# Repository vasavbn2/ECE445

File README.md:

# ECE445
This is our repo for our ECE445 Key FOB project!

## Week of 9/23/24
Discussed our proposal in meeting with our TA.
Next steps: Perform tolerance analysis and begin work on design document.

## Week of 9/30/24
Discussed the design document and design review process with our TA. Working on the proposal regrade, including tolerance analysis and ethics.
Next steps: Complete schematics in KiCad so we have complete schematics and BOMs for our 2 boards. Finish composing the design document.

## Week of 10/7/24
Finalized schematics and started layouts

## Week of 10/14/24
Completed fob layout
BOM for fob: https://www.digikey.com/short/3907nrjb

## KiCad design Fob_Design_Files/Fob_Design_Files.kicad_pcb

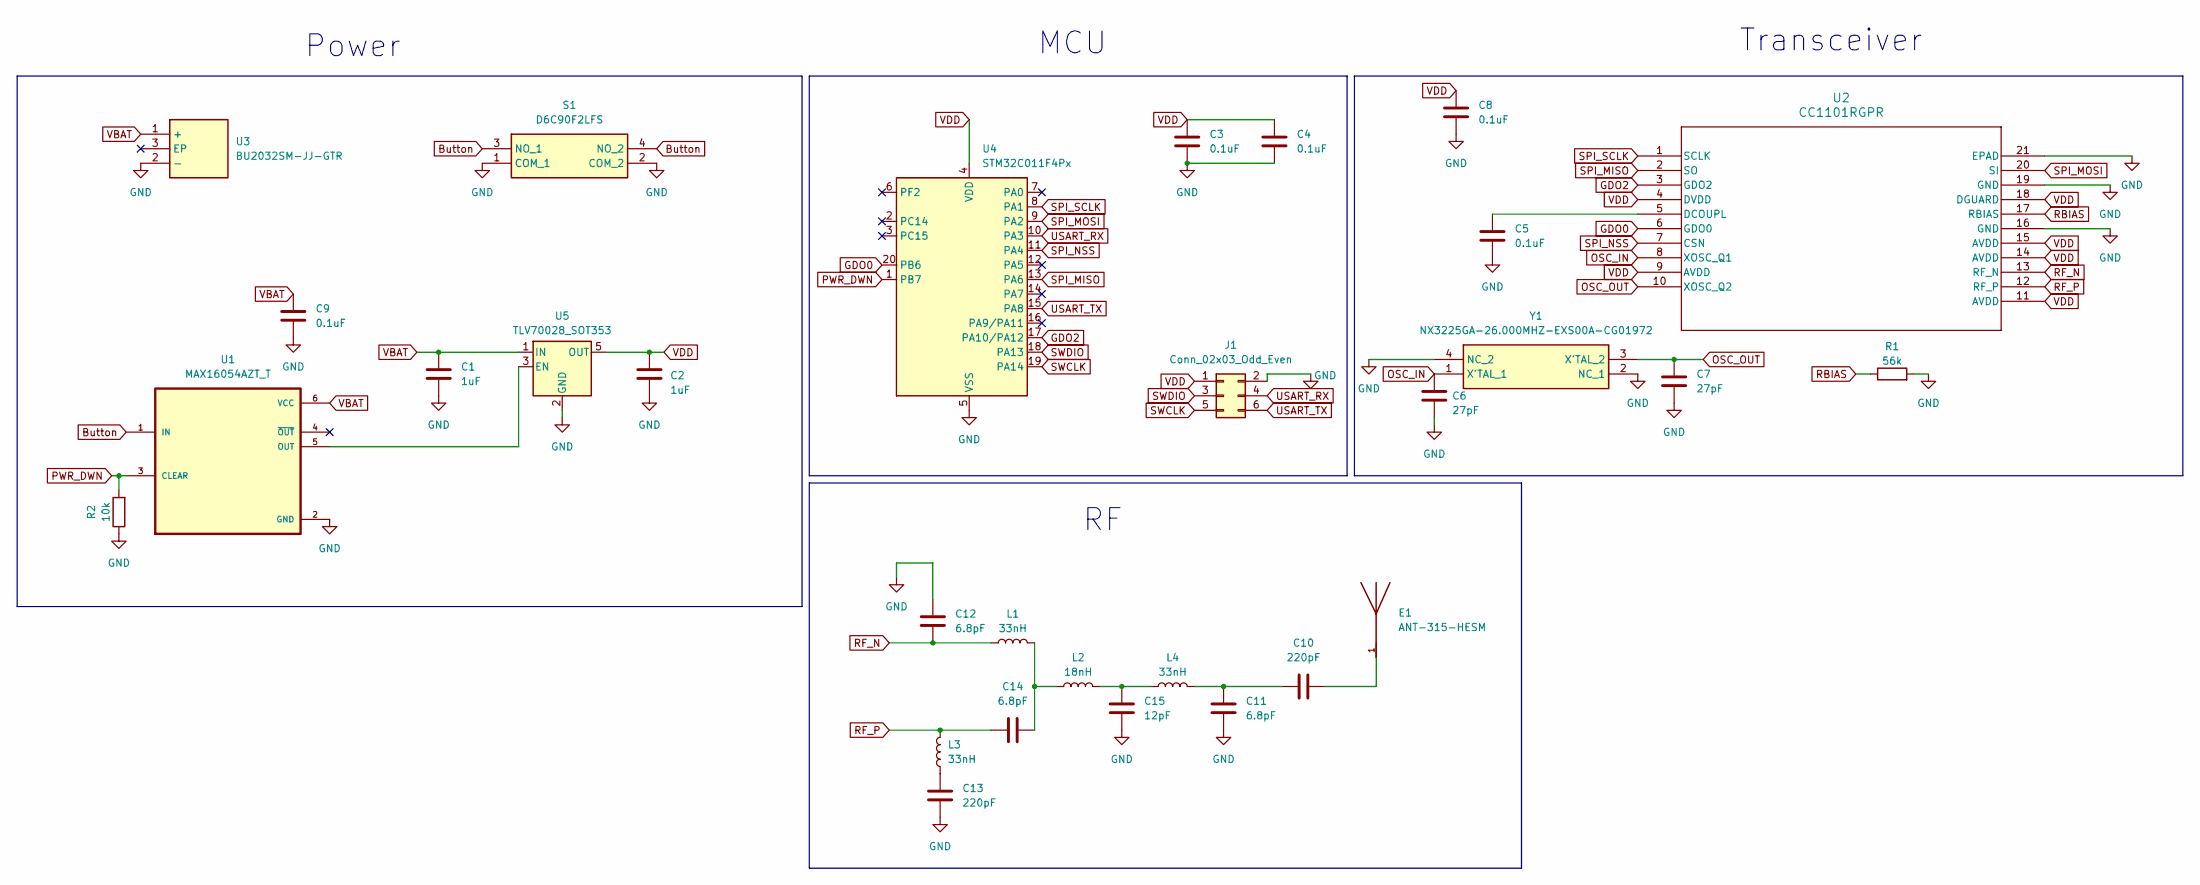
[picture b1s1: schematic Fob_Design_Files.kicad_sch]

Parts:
C1, C2: 1uF; C_0603_1608Metric
C3, C4, C5, C8, C9: 0.1uF; C_0603_1608Metric
C6, C7: 27pF; C_0603_1608Metric
C10, C13: 220pF; C_0603_1608Metric
C11, C12, C14: 6.8pF; C_0603_1608Metric
C15: 12pF; C_0603_1608Metric
E1: ANT-315-HESM; XDCR_ANT-315-HESM; PARTREV B
J1: Conn_02x03_Odd_Even; PinSocket_2x03_P2.54mm_Vertical
L1, L3, L4: 33nH; L_0603_1608Metric
L2: 18nH; L_0603_1608Metric
R1: 56k; L_0603_1608Metric
R2: 10k; L_0603_1608Metric
S1: D6C90F2LFS; Manufacturer_Part_Number D6C90F2LFS; Mouser Part Number 611-D6C90F2LFS
U1: MAX16054AZT_T; SOT95P275X110-6N
U2: CC1101RGPR; RGP20_2P4X2P4
U3: BU2032SM-JJ-GTR; BU2032SMJJGTR; Manufacturer_Part_Number BU2032SM-JJ-GTR
U4: STM32C011F4Px; TSSOP-20_4.4x6.5mm_P0.65mm
U5: TLV70028_SOT353; SOT-353_SC-70-5
Y1: NX3225GA-26.000MHZ-EXS00A-CG01972; NX3225GA16000MSTDCRG1; Mouser Part Number 344-NX3225GA26MHZEXS

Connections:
Button: S1.3 (NO_1), S1.4 (NO_2), U1.1 (IN)
GDO0: U2.6 (GDO0), U4.20 (PB6)
GDO2: U2.3 (GDO2), U4.17 (PA10/PA12)
GND: C1.2, C2.2, C3.2, C4.2, C5.2, C6.2, C7.2, C8.2, C9.2, C11.1, C12.2, C13.1, C15.1, J1.2, R1.2, R2.1, S1.1 (COM_1), S1.2 (COM_2), U1.2 (GND), U2.16 (GND), U2.19 (GND), U2.21 (EPAD), U3.2 (-), U4.5 (VSS), U5.2 (GND), Y1.2 (NC_1), Y1.4 (NC_2)
unnamed: C10.1, C11.2, L4.2
unnamed: C10.2, E1.1
unnamed: C13.2, L3.1
unnamed: C14.1, L1.2, L2.1
unnamed: C15.2, L2.2, L4.1
unnamed: U1.5 (OUT), U5.3 (EN)
unnamed: C5.1, U2.5 (DCOUPL)
OSC_IN: C6.1, U2.8 (XOSC_Q1), Y1.1 (X'TAL_1)
OSC_OUT: C7.1, U2.10 (XOSC_Q2), Y1.3 (X'TAL_2)
PWR_DWN: R2.2, U1.3 (CLEAR), U4.1 (PB7)
RBIAS: R1.1, U2.17 (RBIAS)
RF_N: C12.1, L1.1, U2.13 (RF_N)
RF_P: C14.2, L3.2, U2.12 (RF_P)
SPI_MISO: U2.2 (SO), U4.13 (PA6)
SPI_MOSI: U2.20 (SI), U4.9 (PA2)
SPI_NSS: U2.7 (CSN), U4.11 (PA4)
SPI_SCLK: U2.1 (SCLK), U4.8 (PA1)
SWCLK: J1.5, U4.19 (PA14)
SWDIO: J1.3, U4.18 (PA13)
USART_RX: J1.4, U4.10 (PA3)
USART_TX: J1.6, U4.15 (PA8)
VBAT: C1.1, C9.1, U1.6 (VCC), U3.1 (+), U5.1 (IN)
VDD: C2.1, C3.1, C4.1, C8.1, J1.1, U2.4 (DVDD), U2.9 (AVDD), U2.11 (AVDD), U2.14 (AVDD), U2.15 (AVDD), U2.18 (DGUARD), U4.4 (VDD), U5.5 (OUT)

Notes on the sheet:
Power
MCU
Transceiver

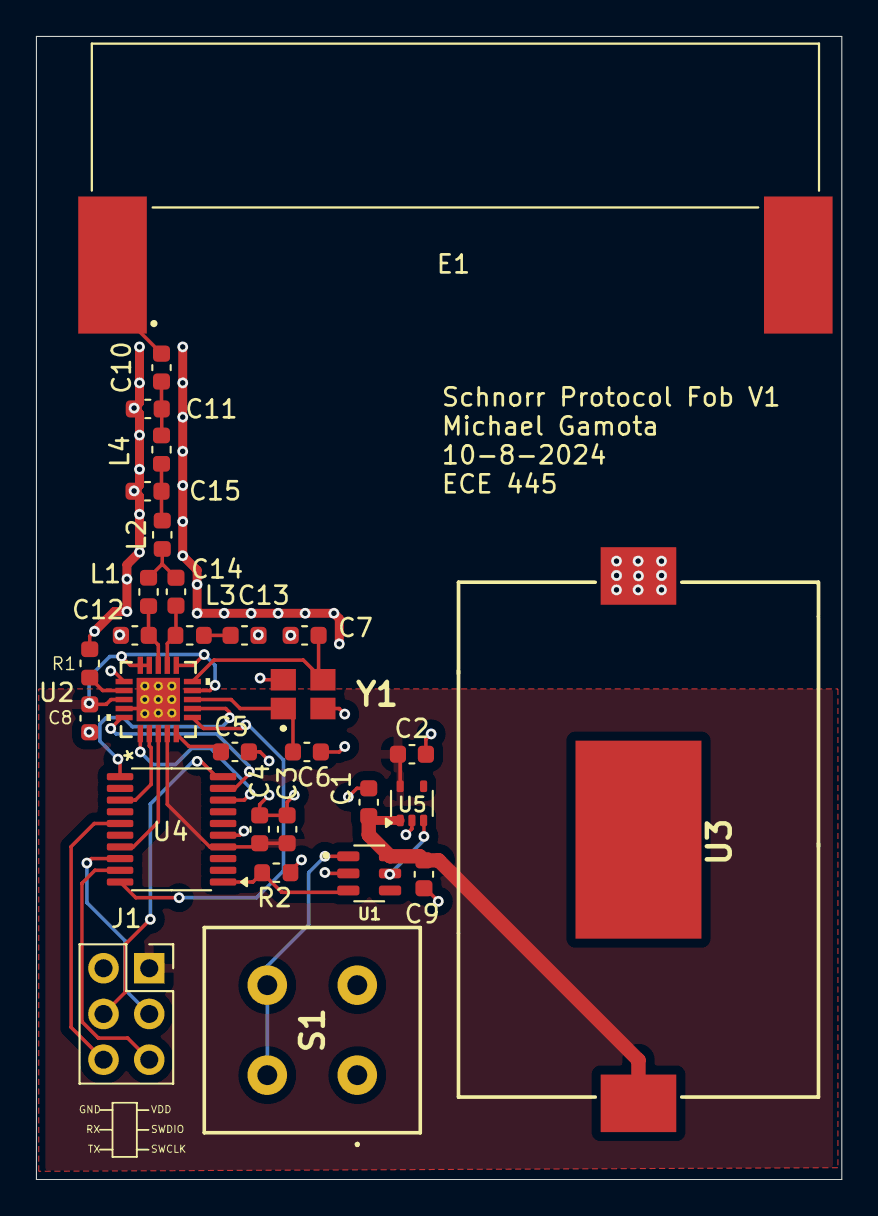
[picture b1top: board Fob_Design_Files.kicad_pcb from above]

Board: 2 copper layers, 44.7 x 63.5 mm, 30 parts (0 on the bottom side), 27 nets.

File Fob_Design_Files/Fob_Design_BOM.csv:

Reference,Value,Datasheet,Footprint,Qty,DNP
"C1,C2",1uF,~,Capacitor_SMD:C_0603_1608Metric,2,
"C3,C4,C5,C8,C9",0.1uF,~,Capacitor_SMD:C_0603_1608Metric,5,
"C6,C7",27pF,~,Capacitor_SMD:C_0603_1608Metric,2,
"C10,C13",220pF,~,Capacitor_SMD:C_0603_1608Metric,2,
"C11,C12,C14",6.8pF,~,Capacitor_SMD:C_0603_1608Metric,3,
C15,12pF,~,Capacitor_SMD:C_0603_1608Metric,1,
E1,ANT-315-HESM,,ANT-315-HESM:XDCR_ANT-315-HESM,1,
J1,Conn_02x03_Odd_Even,~,Connector_PinSocket_2.54mm:PinSocket_2x03_P2.54mm_Vertical,1,
"L1,L3,L4",33nH,~,Inductor_SMD:L_0603_1608Metric,3,
L2,18nH,~,Inductor_SMD:L_0603_1608Metric,1,
R1,56k,~,Inductor_SMD:L_0603_1608Metric,1,
R2,10k,~,Inductor_SMD:L_0603_1608Metric,1,
S1,D6C90F2LFS,https://www.ckswitches.com/media/1341/d6.pdf,SamacSys_Parts:D6C90F2LFS,1,
U1,MAX16054AZT_T,,MAX16054AZT_T:SOT95P275X110-6N,1,
U2,CC1101RGPR,CC1101RGPR,CC1101:RGP20_2P4X2P4,1,
U3,BU2032SM-JJ-GTR,https://datasheet.datasheetarchive.com/originals/dk/DKDS-14/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,SamacSys_Parts:BU2032SMJJGTR,1,
U4,STM32C011F4Px,https://www.st.com/resource/en/datasheet/stm32c011f4.pdf,Package_SO:TSSOP-20_4.4x6.5mm_P0.65mm,1,
U5,TLV70028_SOT353,http://www.ti.com/lit/ds/symlink/tlv700.pdf,Package_TO_SOT_SMD:SOT-353_SC-70-5,1,
Y1,NX3225GA-26.000MHZ-EXS00A-CG01972,https://media.digikey.com/pdf/Data%20Sheets/NDK%20PDFs/NX3225GA.pdf,SamacSys_Parts:NX3225GA16000MSTDCRG1,1,

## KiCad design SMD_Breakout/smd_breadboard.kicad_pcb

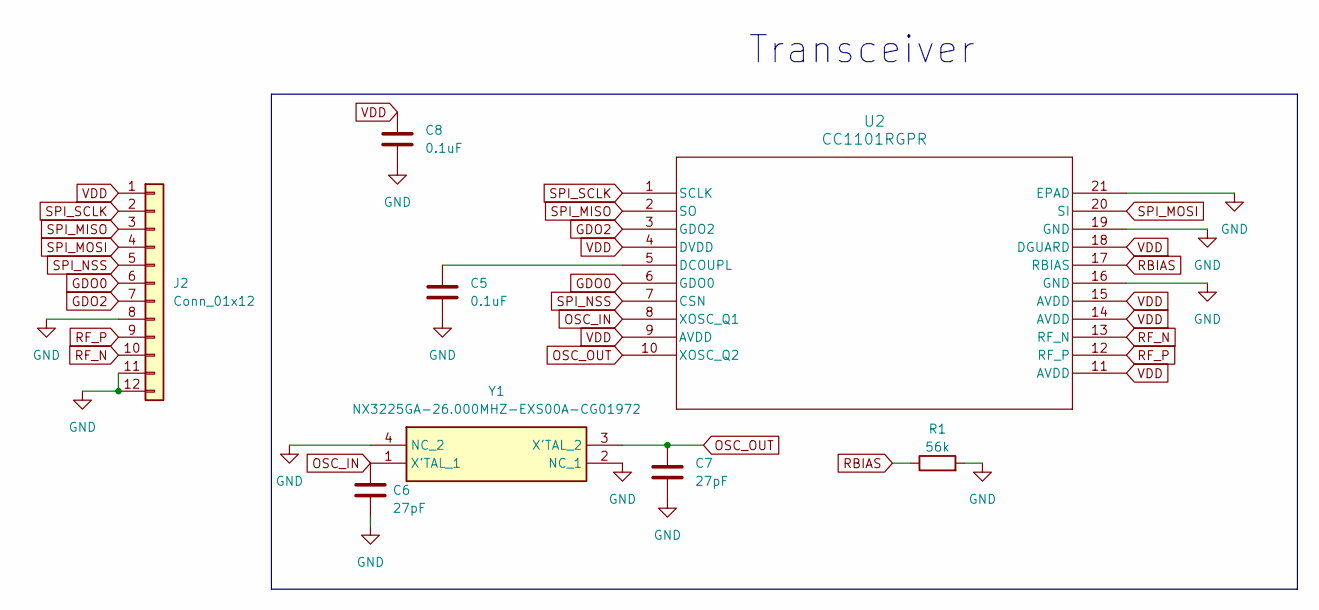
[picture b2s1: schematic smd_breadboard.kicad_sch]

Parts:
C5, C8: 0.1uF; C_0603_1608Metric
C6, C7: 27pF; C_0603_1608Metric
J2: Conn_01x12; PinSocket_1x12_P2.54mm_Horizontal
R1: 56k; L_0603_1608Metric
U2: CC1101RGPR; Texas_RGP0020H_VQFN-20-1EP_4x4mm_P0.5mm_EP2.4x2.4mm
Y1: NX3225GA-26.000MHZ-EXS00A-CG01972; NX3225GA16000MSTDCRG1; Mouser Part Number 344-NX3225GA26MHZEXS

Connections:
GDO0: J2.6, U2.6 (GDO0)
GDO2: J2.7, U2.3 (GDO2)
GND: C5.2, C6.2, C7.2, C8.2, J2.8, J2.11, J2.12, R1.2, U2.16 (GND), U2.19 (GND), U2.21 (EPAD), Y1.2 (NC_1), Y1.4 (NC_2)
unnamed: C5.1, U2.5 (DCOUPL)
OSC_IN: C6.1, U2.8 (XOSC_Q1), Y1.1 (X'TAL_1)
OSC_OUT: C7.1, U2.10 (XOSC_Q2), Y1.3 (X'TAL_2)
RBIAS: R1.1, U2.17 (RBIAS)
RF_N: J2.10, U2.13 (RF_N)
RF_P: J2.9, U2.12 (RF_P)
SPI_MISO: J2.3, U2.2 (SO)
SPI_MOSI: J2.4, U2.20 (SI)
SPI_NSS: J2.5, U2.7 (CSN)
SPI_SCLK: J2.2, U2.1 (SCLK)
VDD: C8.1, J2.1, U2.4 (DVDD), U2.9 (AVDD), U2.11 (AVDD), U2.14 (AVDD), U2.15 (AVDD), U2.18 (DGUARD)

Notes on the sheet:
Transceiver

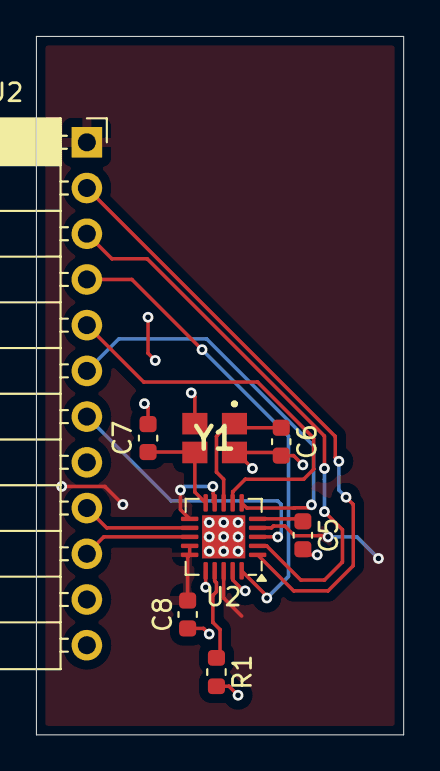
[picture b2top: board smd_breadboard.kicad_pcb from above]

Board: 2 copper layers, 20.4 x 38.8 mm, 8 parts (0 on the bottom side), 14 nets.

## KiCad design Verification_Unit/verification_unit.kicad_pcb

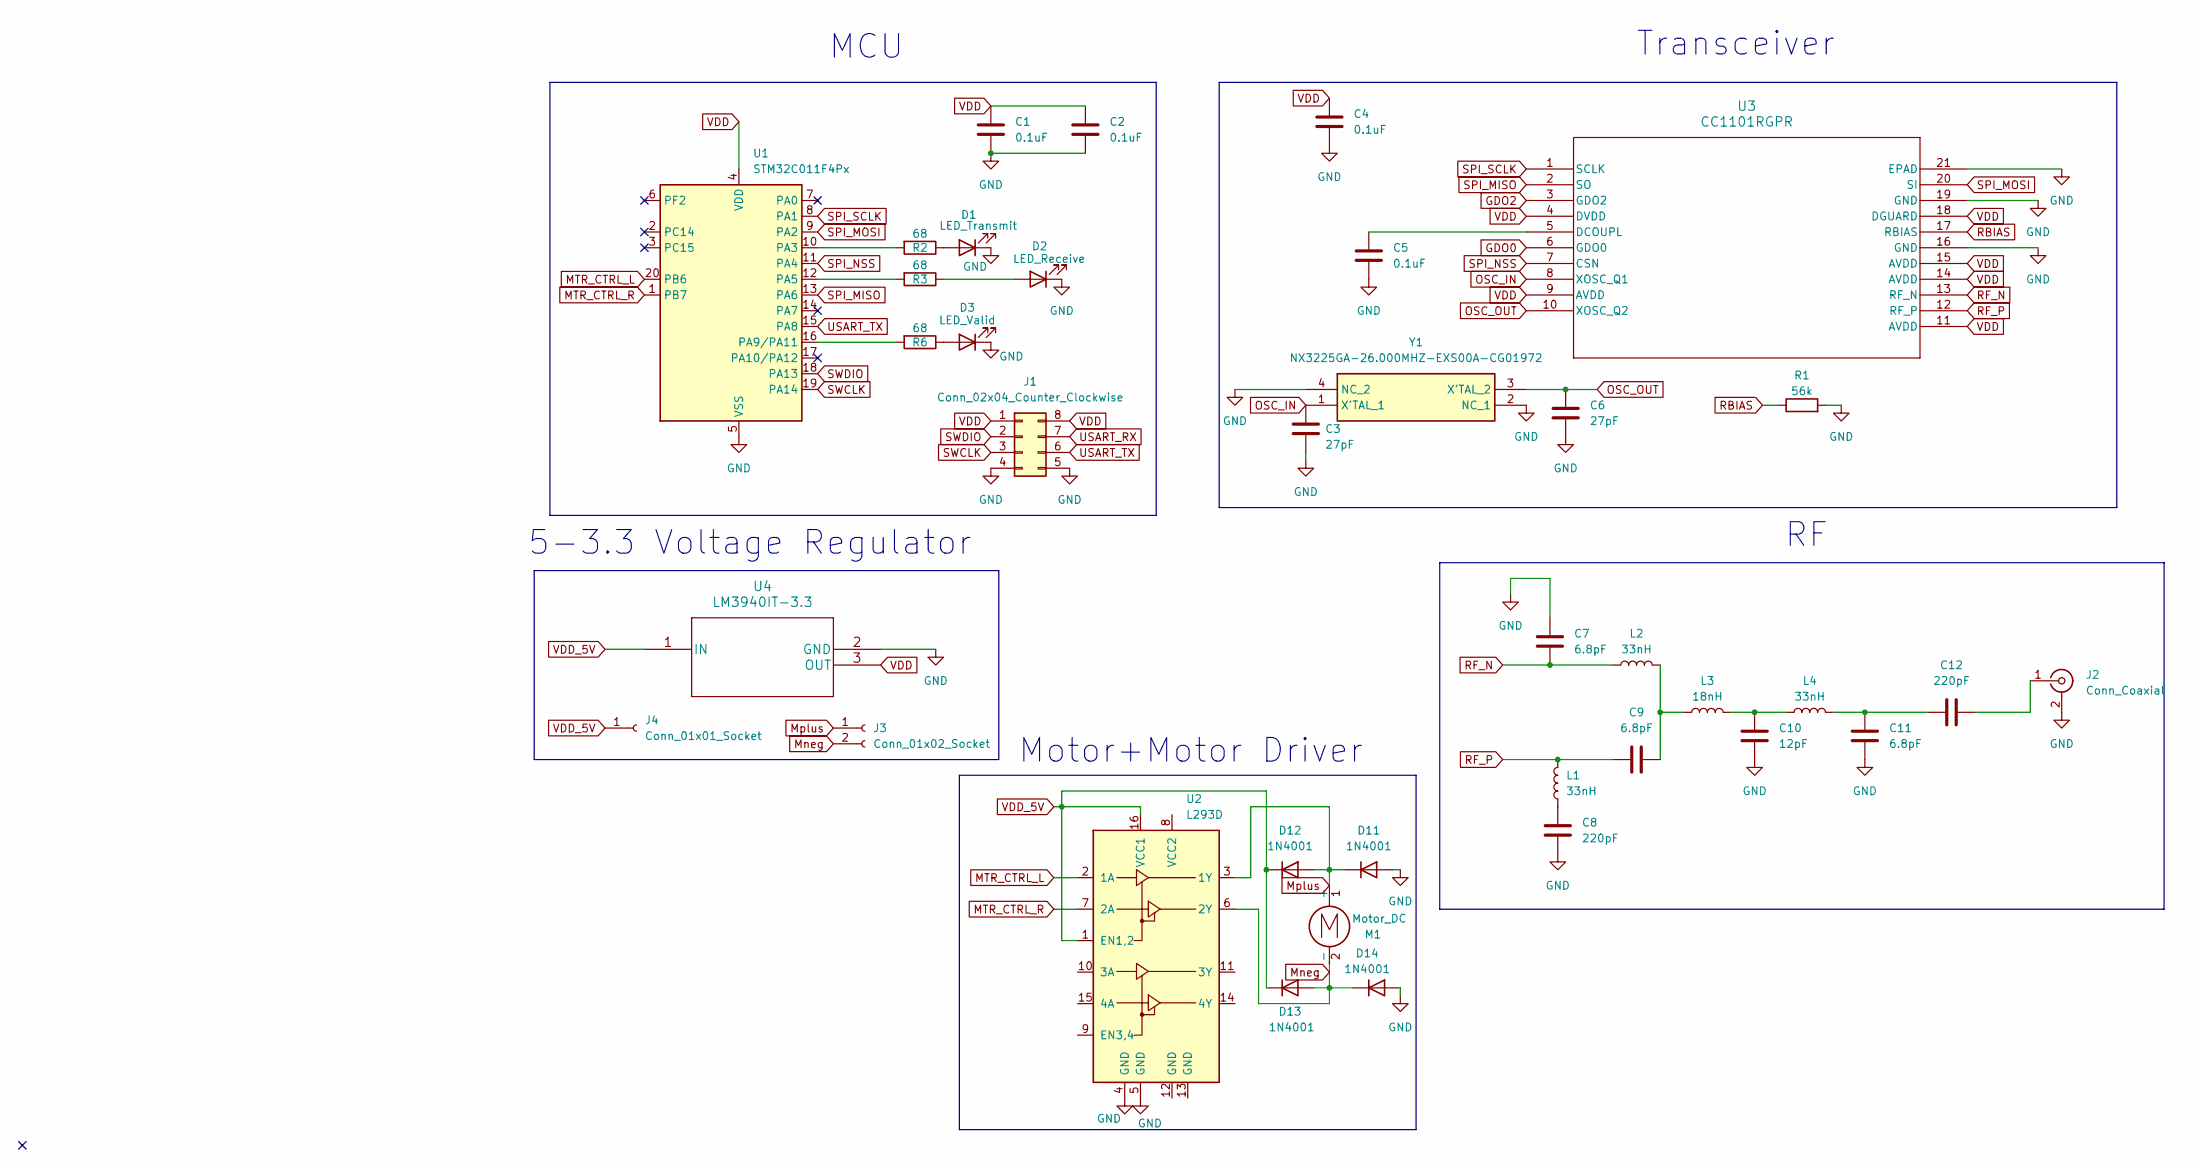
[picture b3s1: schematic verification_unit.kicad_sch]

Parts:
C1, C2, C4, C5: 0.1uF; C_0805_2012Metric
C3, C6: 27pF; C_0805_2012Metric
C7, C9, C11: 6.8pF; C_0805_2012Metric
C8, C12: 220pF; C_0805_2012Metric
C10: 12pF; C_0805_2012Metric
D1: LED_Transmit; LED_0805_2012Metric
D2: LED_Receive; LED_0805_2012Metric
D3: LED_Valid; LED_0805_2012Metric
D11, D12, D13, D14: 1N4001; D_0805_2012Metric
J1: Conn_02x04_Counter_Clockwise; PinSocket_2x04_P2.54mm_Vertical
J2: Conn_Coaxial; SMA_Amphenol_901-143_Horizontal
J3: Conn_01x02_Socket; PinSocket_1x02_P2.54mm_Vertical
J4: Conn_01x01_Socket; PinSocket_1x01_P2.54mm_Vertical
L1, L2, L4: 33nH; L_0805_2012Metric
L3: 18nH; L_0805_2012Metric
M1: Motor_DC
R1: 56k; C_0805_2012Metric
R2, R3, R6: 68; R_0805_2012Metric
U1: STM32C011F4Px; TSSOP-20_4.4x6.5mm_P0.65mm
U2: L293D; DIP-16_W7.62mm
U3: CC1101RGPR; RGP20_2P4X2P4
U4: LM3940IT-3.3
Y1: NX3225GA-26.000MHZ-EXS00A-CG01972; NX3225GA16000MSTDCRG1; Mouser Part Number 344-NX3225GA26MHZEXS

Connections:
GDO0: U3.6 (GDO0)
GDO2: U3.3 (GDO2)
GND: C1.2, C2.2, C3.2, C4.2, C5.2, C6.2, C7.2, C8.1, C10.1, C11.1, D1.1 (K), D2.1 (K), D3.1 (K), D11.2 (A), D14.2 (A), J1.4, J1.5, J2.2 (Ext), R1.2, U1.5 (VSS), U2.4 (GND), U2.5 (GND), U3.16 (GND), U3.19 (GND), U3.21 (EPAD), U4.2 (GND), Y1.2 (NC_1), Y1.4 (NC_2)
MTR_CTRL_L: U1.20 (PB6), U2.2 (1A)
MTR_CTRL_R: U1.1 (PB7), U2.7 (2A)
Mneg: D13.2 (A), D14.1 (K), J3.2, M1.2 (-), U2.6 (2Y)
Mplus: D11.1 (K), D12.2 (A), J3.1, M1.1 (+), U2.3 (1Y)
unnamed: C8.2, L1.1
unnamed: C9.1, L2.2, L3.1
unnamed: C10.2, L3.2, L4.1
unnamed: C11.2, C12.1, L4.2
unnamed: D1.2 (A), R2.1
unnamed: D2.2 (A), R3.1
unnamed: D3.2 (A), R6.1
unnamed: C12.2, J2.1 (In)
unnamed: R2.2, U1.10 (PA3)
unnamed: R3.2, U1.12 (PA5)
unnamed: R6.2, U1.16 (PA9/PA11)
unnamed: C5.1, U3.5 (DCOUPL)
OSC_IN: C3.1, U3.8 (XOSC_Q1), Y1.1 (X'TAL_1)
OSC_OUT: C6.1, U3.10 (XOSC_Q2), Y1.3 (X'TAL_2)
RBIAS: R1.1, U3.17 (RBIAS)
RF_N: C7.1, L2.1, U3.13 (RF_N)
RF_P: C9.2, L1.2, U3.12 (RF_P)
SPI_MISO: U1.13 (PA6), U3.2 (SO)
SPI_MOSI: U1.9 (PA2), U3.20 (SI)
SPI_NSS: U1.11 (PA4), U3.7 (CSN)
SPI_SCLK: U1.8 (PA1), U3.1 (SCLK)
SWCLK: J1.3, U1.19 (PA14)
SWDIO: J1.2, U1.18 (PA13)
USART_RX: J1.7
USART_TX: J1.6, U1.15 (PA8)
VDD: C1.1, C2.1, C4.1, J1.1, J1.8, U1.4 (VDD), U3.4 (DVDD), U3.9 (AVDD), U3.11 (AVDD), U3.14 (AVDD), U3.15 (AVDD), U3.18 (DGUARD), U4.3 (OUT)
VDD_5V: D12.1 (K), D13.1 (K), J4.1, U2.1 (EN1,2), U2.16 (VCC1), U4.1 (IN)

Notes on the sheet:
Transceiver
MCU
Motor+Motor Driver
5-3.3 Voltage Regulator

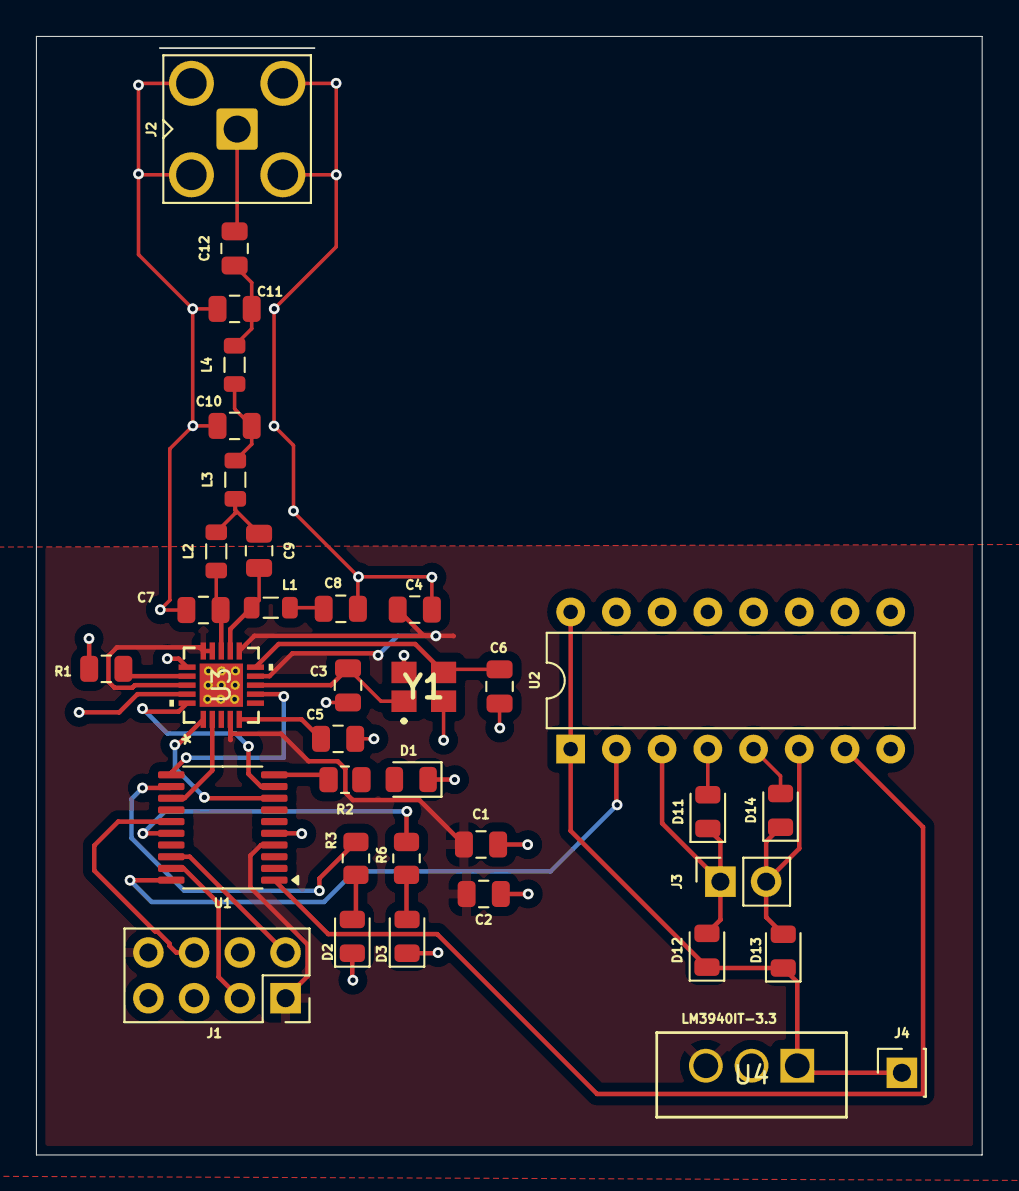
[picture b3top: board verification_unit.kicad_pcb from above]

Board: 2 copper layers, 52.5 x 62.1 mm, 36 parts (0 on the bottom side), 31 nets.

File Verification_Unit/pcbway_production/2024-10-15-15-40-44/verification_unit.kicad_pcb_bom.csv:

Designator,Quantity,Value,Footprint,Package,MPN,DNP,Mount_Type,Description,Sim.Device,Sim.Pins,Height,Mouser Part Number,Mouser Price/Stock,Manufacturer_Name
"C1, C2, C4, C5",4,0.1uF,C_0805_2012Metric,,,,smt,Unpolarized capacitor,,,,,,
C10,1,12pF,C_0805_2012Metric,,,,smt,Unpolarized capacitor,,,,,,
"C11, C7, C9",3,6.8pF,C_0805_2012Metric,,,,smt,Unpolarized capacitor,,,,,,
"C12, C8",2,220pF,C_0805_2012Metric,,,,smt,Unpolarized capacitor,,,,,,
"C3, C6",2,27pF,C_0805_2012Metric,,,,smt,Unpolarized capacitor,,,,,,
D1,1,LED_Transmit,LED_0805_2012Metric,,,,smt,Light emitting diode,,,,,,
"D11, D12, D13, D14",4,1N4001,D_0805_2012Metric,,,,smt,"50V 1A General Purpose Rectifier Diode, DO-41",D,1=K 2=A,,,,
D2,1,LED_Receive,LED_0805_2012Metric,,,,smt,Light emitting diode,,,,,,
D3,1,LED_Valid,LED_0805_2012Metric,,,,smt,Light emitting diode,,,,,,
J1,1,Conn_02x04_Counter_Clockwise,PinSocket_2x04_P2.54mm_Vertical,,,,tht,"Generic connector, double row, 02x04, counter clockwise pin numbering scheme (similar to DIP package numbering), script generated (kicad-library-utils/schlib/autogen/connector/)",,,,,,
J2,1,Conn_Coaxial,SMA_Amphenol_901-143_Horizontal,,,,tht,"coaxial connector (BNC, SMA, SMB, SMC, Cinch/RCA, LEMO, ...)",,,,,,
J3,1,Conn_01x02_Socket,PinSocket_1x02_P2.54mm_Vertical,,,,tht,"Generic connector, single row, 01x02, script generated",,,,,,
J4,1,Conn_01x01_Socket,PinSocket_1x01_P2.54mm_Vertical,,,,tht,"Generic connector, single row, 01x01, script generated",,,,,,
"L1, L2, L4",3,33nH,L_0805_2012Metric,,,,smt,Inductor,,,,,,
L3,1,18nH,L_0805_2012Metric,,,,smt,Inductor,,,,,,
R1,1,56k,C_0805_2012Metric,,,,smt,Resistor,,,,,,
"R2, R3, R6",3,68,R_0805_2012Metric,,,,smt,Resistor,,,,,,
U1,1,STM32C011F4Px,TSSOP-20_4.4x6.5mm_P0.65mm,,,,smt,"STMicroelectronics Arm Cortex-M0+ MCU, 16KB flash, 6KB RAM, 48 MHz, 2.0-3.6V, 18 GPIO, TSSOP20",,,,,,
U2,1,L293D,DIP-16_W7.62mm,,,,tht,Quadruple Half-H Drivers,,,,,,
U3,1,CC1101RGPR,RGP20_2P4X2P4,,,,smt,,,,,,,
U4,1,LM3940IT-3.3,LM3940IT-3.3,,,,tht,,,,,,,
Y1,1,NX3225GA-26.000MHZ-EXS00A-CG01972,NX3225GA16000MSTDCRG1,,NX3225GA-26.000MHZ-EXS00A-CG01972,,smt,Crystals CRYSTAL 26MHZ 10PF SMD,,,0.9,344-NX3225GA26MHZEXS,https://www.mouser.co.uk/ProductDetail/NDK/NX3225GA-26.000MH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,NDK

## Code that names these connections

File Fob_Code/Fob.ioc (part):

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Mcu.Name=STM32C011F(4-6)Px
Mcu.Package=TSSOP20
Mcu.UserName=STM32C011F4Px
PA1.Mode=Full_Duplex_Master
PA1.Signal=SPI1_SCK
PA12\ [PA10].GPIOParameters=GPIO_Label
PA12\ [PA10].GPIO_Label=GDO2
PA12\ [PA10].Signal=GPXTI12
PA13.Mode=Serial_Wire
PA13.Signal=DEBUG_SWDIO
PA14-BOOT0.Mode=Serial_Wire
PA14-BOOT0.Signal=DEBUG_SWCLK
PA2.Mode=Full_Duplex_Master
PA2.Signal=SPI1_MOSI
PA3.Mode=Asynchronous
PA3.Signal=USART2_RX
PA4.GPIOParameters=GPIO_Label
PA4.GPIO_Label=CS
PA4.Signal=GPIO_Output
PA6.GPIOParameters=GPIO_Label
PA6.GPIO_Label=MISO
PA6.Mode=Full_Duplex_Master
PA6.Signal=SPI1_MISO
PA8.Mode=Asynchronous
PA8.Signal=USART2_TX
PB6.GPIOParameters=GPIO_Label
PB6.GPIO_Label=GDO0
PB6.Signal=GPIO_Input
RCC.HSE_VALUE=8000000
RCC.SYSCLKFreq_VALUE=12000000
board=custom

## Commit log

2024-10-01 Created project for fob
2024-10-02 Finished schematic
2024-10-02 Completed schematic
2024-10-02 Updated readme:
2024-10-02 Minor fob schematic changes
2024-10-03 Added UART and indicator LEDs
2024-10-03 Tolerance anaylsis LaTeX
2024-10-03 Schnorr explanation LaTex
2024-10-03 Adding BOM
2024-10-03 verification unit
2024-10-03 please work
2024-10-09 Done with fob layout
2024-10-09 Minor changes
2024-10-09 Unlocking fob files
2024-10-14 New gerbers
2024-10-29 bruh
2024-10-29 Adding schnorr Python implementation
2024-11-10 Adding code
2024-11-18 adding software
2024-12-02 schnorr code

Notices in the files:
parts and their libraries:
Copyright 2016 Accelerated Designs. All rights reserved.
